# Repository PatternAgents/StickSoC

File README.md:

StickSoC
=============

PatternAgents StickSoC - add on boards for the Cypress CY8CKIT-049 (PSoC4)

[  
*PatternAgents StickSoC*](http://www.patternagents.com/projects/StickSoC.html)

The PatternAgents StickSoC allows the Cypress CY8CKIT-049 board to accept Arduino type Shields.

Features:

        DC Barrel Jack for Providing VIN, 12Vdc-16Vdc to Shields that need it.

        PTC Resetable Fuse for VIN
	
        USB/5.0Vdc to 3.3Volt Voltage Regulator
	
	Arduino Uno/Leonardo Compatible Shield

You can read more about the PSoC4 Integrated Circuit used here : http://www.cypress.com/?mpn=CY8C4245AXI-483

[  
*Licensing CC BY-NC-SA 4.0*](http://creativecommons.org/licenses/by-nc-sa/4.0/)

PatternAgents uses the increasingly popular business model called "Dual Licensing" 
in which both the open source software distribution mechanism and traditional commercial software distribution models are combined.

Open Source Projects:        

If you are developing and distributing open source applications under the Creative Commons CC BY-NC-SA 4.0, 
as published by the Creative Commons Foundation, then you are free to use the PatternAgents hardware/software under the CC BY-NC-SA 4.0 license. 
Please note that CC BY-NC-SA 4.0 requires that all modifications to the original code as well as all Derivative Works 
must also be released under the terms of the CC BY-NC-SA 4.0 license.

Closed Source Projects:

If you are developing and distributing traditional closed source or commercial applications, 
you must purchase a PatternAgents commercial use license, 
which is specifically designed for users interested in retaining the proprietary status of their designs and code. 
All PatternAgents commercial licenses expressly supersede the CC BY-NC-SA 4.0 license. 
This means that when you license the PatternAgents software under a commercial license, 
you specifically do not use the software under the CC BY-NC-SA 4.0 license and therefore you are not subject to any of its terms.
        
If you would like to use our designs for your own personal or educational use, have at it! 

Our public design repository is available at <a href="https://github.com/patternagents">Github</a>.

If you would like to produce our designs for commercial use, or as products for sale, 
please contact us to arrange for a Commercial Use license. We have many other designs, 
as well as options and extras that are not released publicly. 
We will also customize designs, firmware, and software for a reasonable fee, just contact us to discuss your requirements.

THIS SOFTWARE IS PROVIDED BY THE CONTRIBUTORS "AS IS" AND WITHOUT ANY EXPRESS OR IMPLIED WARRANTIES, 
INCLUDING, BUT NOT LIMITED TO, THE IMPLIED WARRANTIES OF MERCHANTABILITY AND FITNESS FOR A PARTICULAR PURPOSE ARE DISCLAIMED. 
IN NO EVENT SHALL THE COPYRIGHT OWNER OR CONTRIBUTORS BE LIABLE FOR ANY DIRECT, INDIRECT, INCIDENTAL, SPECIAL, EXEMPLARY, 
OR CONSEQUENTIAL DAMAGES (INCLUDING, BUT NOT LIMITED TO, PROCUREMENT OF SUBSTITUTE GOODS OR SERVICES; LOSS OF USE, DATA, 
OR PROFITS; OR BUSINESS INTERRUPTION) HOWEVER CAUSED AND ON ANY THEORY OF LIABILITY, WHETHER IN CONTRACT, 
STRICT LIABILITY, OR TORT (INCLUDING NEGLIGENCE OR OTHERWISE) ARISING IN ANY WAY OUT OF THE USE OF THIS SOFTWARE, 
EVEN IF ADVISED OF THE POSSIBILITY OF SUCH DAMAGE. 

-------------------------------------------------------------------------------------------

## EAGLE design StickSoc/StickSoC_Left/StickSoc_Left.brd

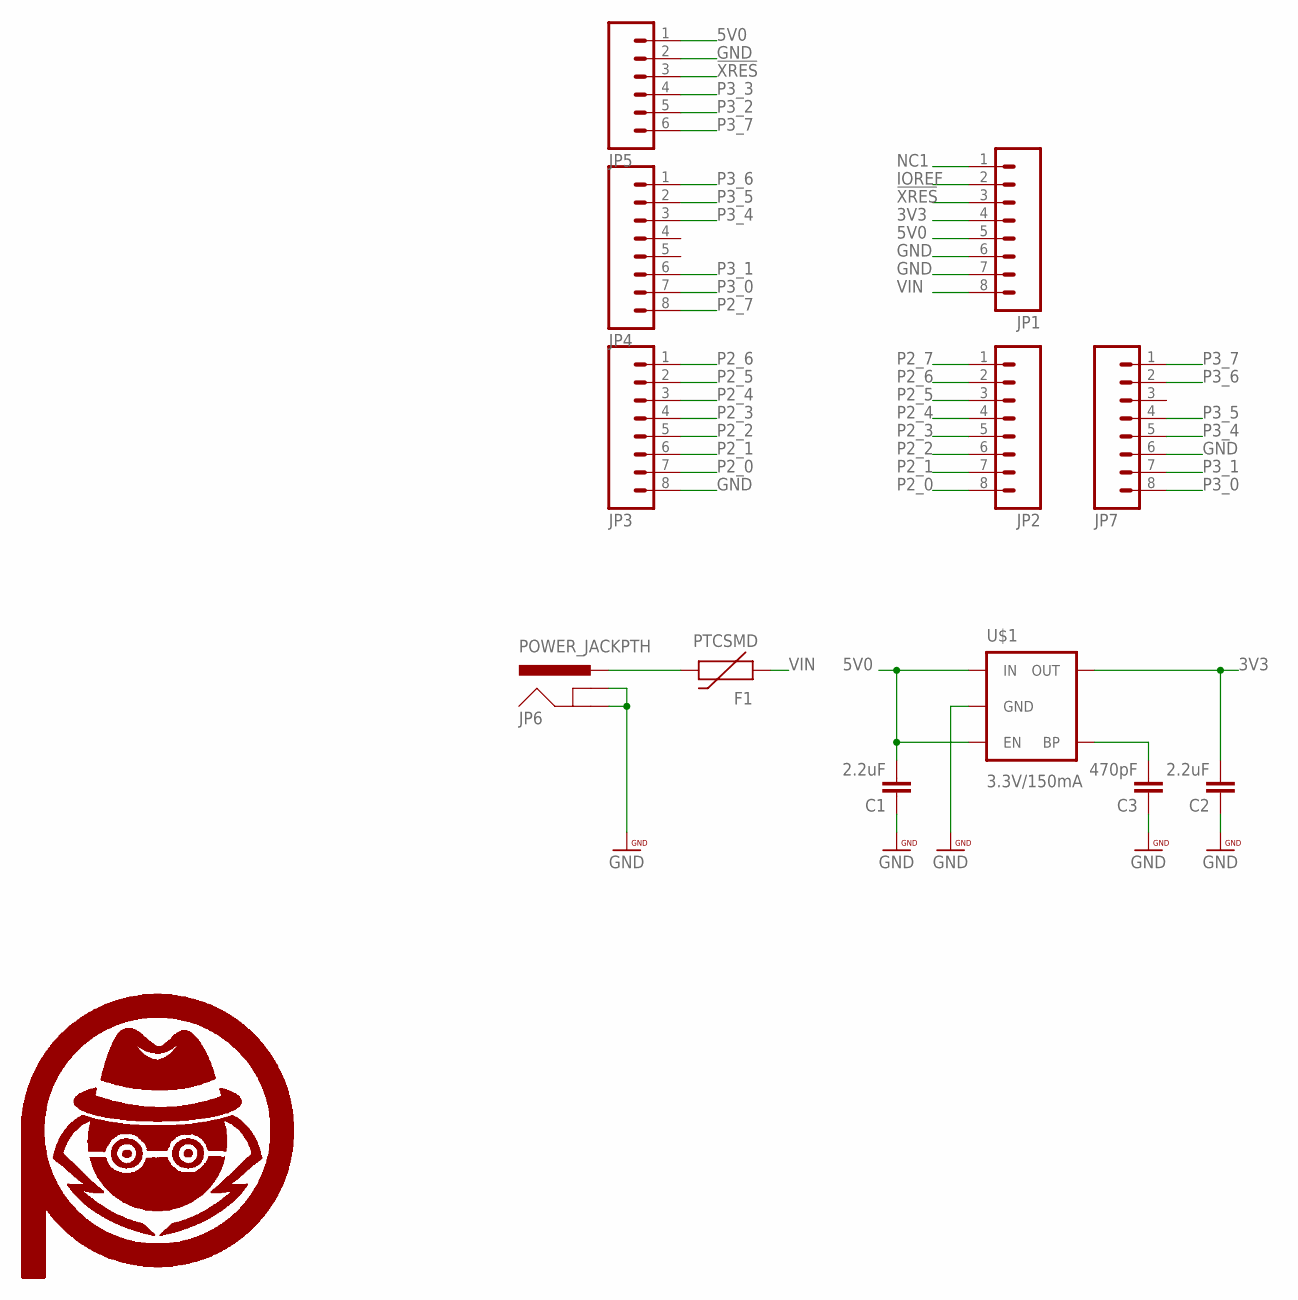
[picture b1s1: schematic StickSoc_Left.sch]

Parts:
C1, C2: 2.2uF; 0805
C3: 470pF; 0805
F1: PTCSMD; PTC-1206
JP1, JP2, JP3, JP4, JP7: M081X08; 1X08
JP5: M06SIP; 1X06
JP6: POWER_JACKPTH; POWER_JACK_PTH
U$1: 3.3V/150mA; SOT23-5
U$7, U$8: PA_LOGO_SYMSMALL; PA_LOGO_AGENT_SMALL_SYM

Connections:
3V3: C2.2, JP1.4, U$1.5 (OUT)
5V0: C1.2, JP1.5, JP5.1, U$1.1 (IN), U$1.3 (EN)
!XRES: JP1.3, JP5.3
GND: C1.1, C2.1, C3.1, JP1.6, JP1.7, JP3.8, JP5.2, JP6.GND, JP6.GNDBREAK, JP7.6, U$1.2 (GND)
IOREF: JP1.2
unnamed: F1.2, JP6.PWR
unnamed: C3.2, U$1.4 (BP)
NC1: JP1.1
P2_0: JP2.8, JP3.7
P2_1: JP2.7, JP3.6
P2_2: JP2.6, JP3.5
P2_3: JP2.5, JP3.4
P2_4: JP2.4, JP3.3
P2_5: JP2.3, JP3.2
P2_6: JP2.2, JP3.1
P2_7: JP2.1, JP4.8
P3_0: JP4.7, JP7.8
P3_1: JP4.6, JP7.7
P3_2: JP5.5
P3_3: JP5.4
P3_4: JP4.3, JP7.5
P3_5: JP4.2, JP7.4
P3_6: JP4.1, JP7.2
P3_7: JP5.6, JP7.1
VIN: F1.1, JP1.8

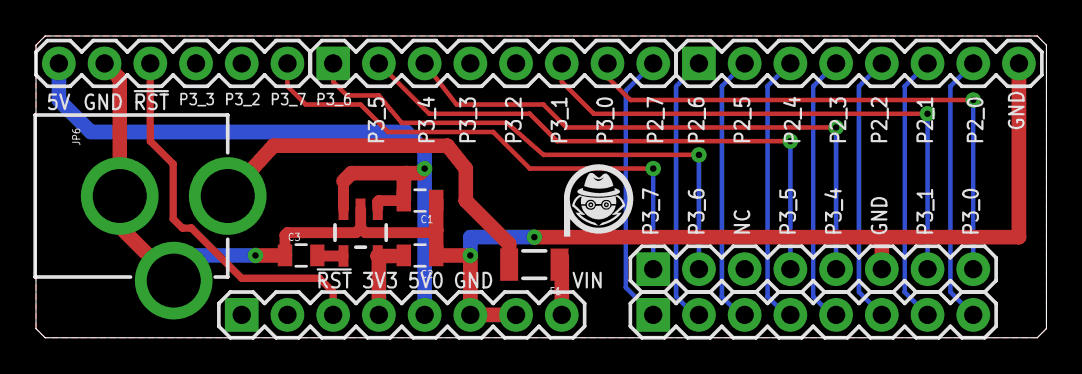
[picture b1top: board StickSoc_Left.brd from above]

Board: 2 copper layers, 56.1 x 16.8 mm, 14 parts (1 on the bottom side), 21 nets.

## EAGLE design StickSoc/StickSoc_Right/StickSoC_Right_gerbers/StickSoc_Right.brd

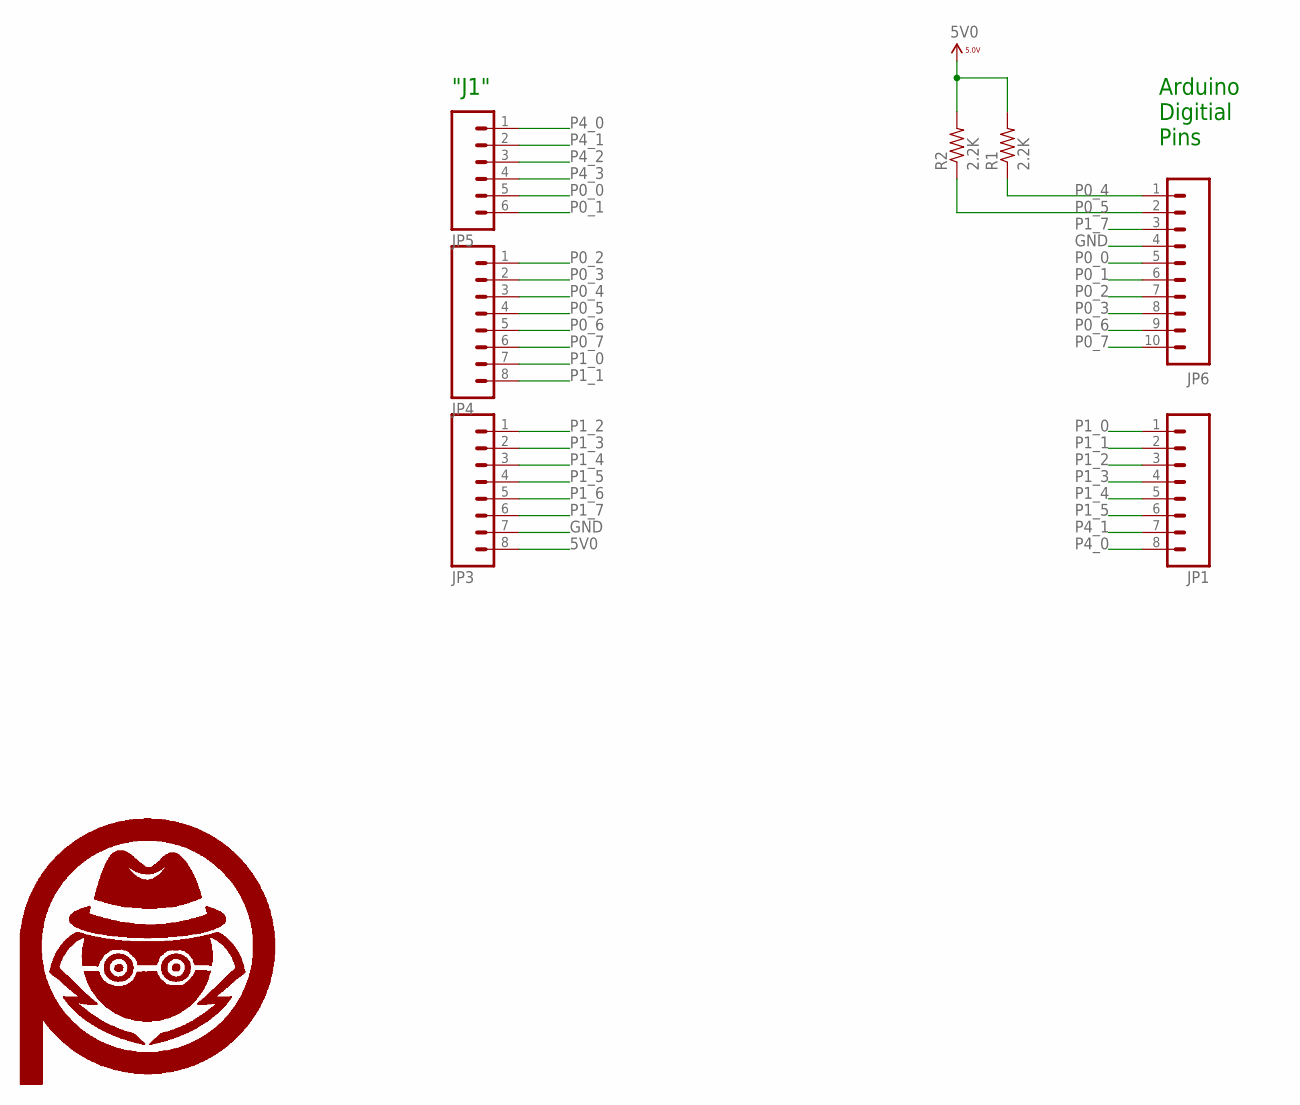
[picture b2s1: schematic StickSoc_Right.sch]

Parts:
JP1, JP3, JP4: M081X08; 1X08
JP5: M06SIP; 1X06
JP6: M10SILK_FEMALE_PTH; 1X10
R1, R2: 2.2K; 0805
U$1, U$2: PA_LOGO_SYMSMALL; PA_LOGO_AGENT_SMALL_SYM

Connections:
5V0: JP3.8, R1.2, R2.2
GND: JP3.7, JP6.4
P0_0: JP5.5, JP6.5
P0_1: JP5.6, JP6.6
P0_2: JP4.1, JP6.7
P0_3: JP4.2, JP6.8
P0_4: JP4.3, JP6.1, R1.1
P0_5: JP4.4, JP6.2, R2.1
P0_6: JP4.5, JP6.9
P0_7: JP4.6, JP6.10
P1_0: JP1.1, JP4.7
P1_1: JP1.2, JP4.8
P1_2: JP1.3, JP3.1
P1_3: JP1.4, JP3.2
P1_4: JP1.5, JP3.3
P1_5: JP1.6, JP3.4
P1_6: JP3.5
P1_7: JP3.6, JP6.3
P4_0: JP1.8, JP5.1
P4_1: JP1.7, JP5.2
P4_2: JP5.3
P4_3: JP5.4

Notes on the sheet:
"J1"
Arduino Digitial Pins

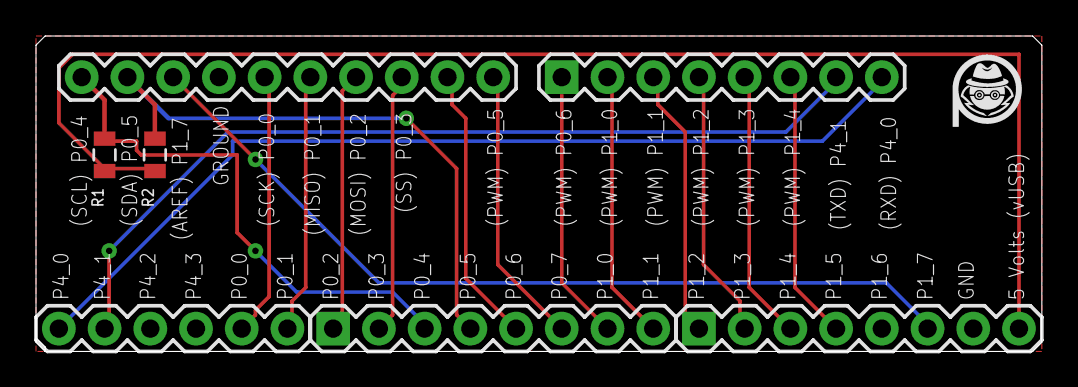
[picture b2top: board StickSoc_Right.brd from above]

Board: 2 copper layers, 55.9 x 17.5 mm, 9 parts (1 on the bottom side), 19 nets.

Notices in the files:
parts and their libraries:
SparkFun-Connectors: Licensing: Creative Commons ShareAlike 4.0 International - https://creativecommons.org/licenses/by-sa/4.0
PatternAgents-Logos: License : http://creativecommons.org/licenses/by-sa/3.0
(Creative Commons 3.0)
